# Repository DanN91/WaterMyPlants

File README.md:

# WaterMyPlants

#### Software and Hardware ( ATMega328P ) system aimed to keep our plants alive for a reasonable amount of time while we enjoy our vacation.

Functionalities ( Strategies, changeable at run-time ):
1. **Manual** mode: turn the water pump on/off via a button push;
2. **Timer** mode: turn the water pump on/off for a specific duration of time and with a specific frequency ( once every x days );
3. **Sensor** mode: monitor the soil moisture and calibrate wetness and dryness levels, then water the plants whenever set dryness level is reached, up to the set wetness level.

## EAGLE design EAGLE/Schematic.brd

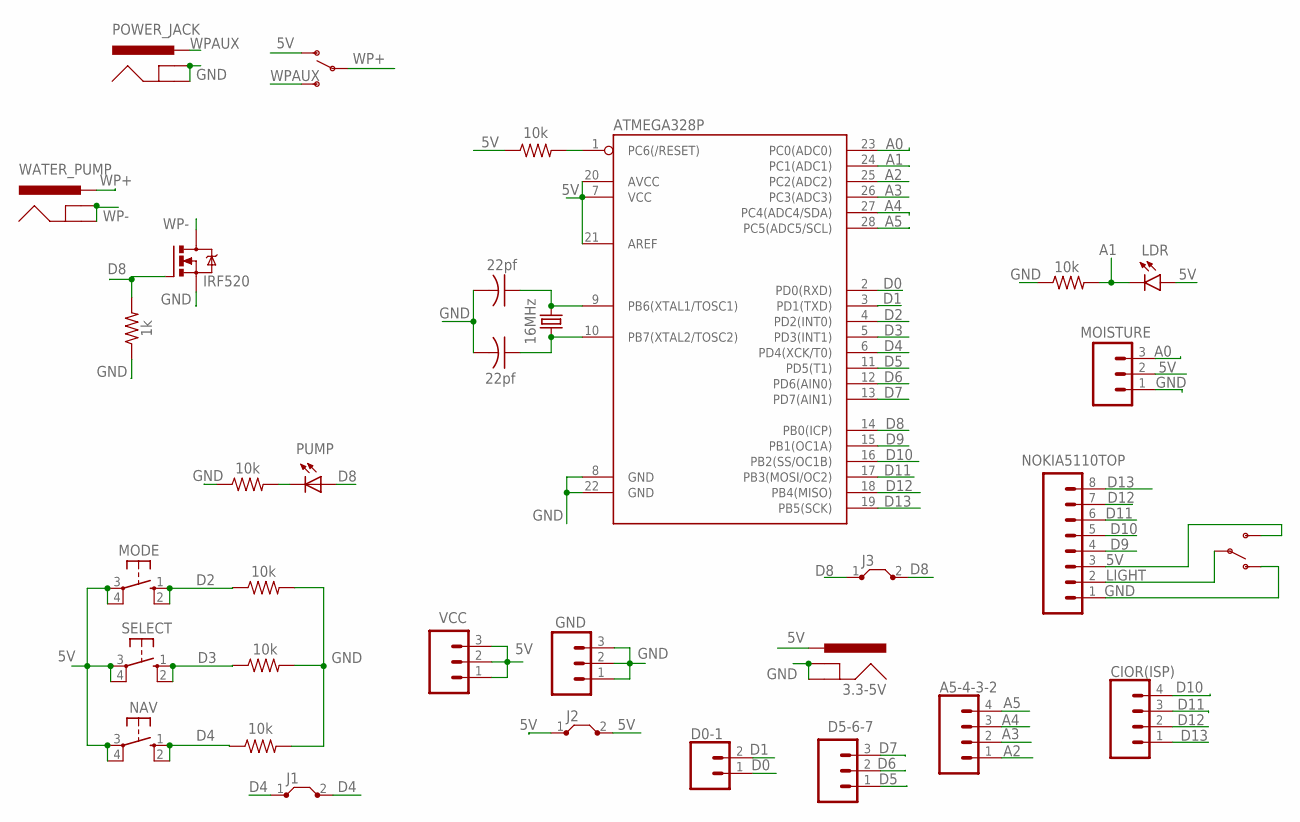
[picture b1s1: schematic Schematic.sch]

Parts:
3.3-5V: POWER_JACK; POWER_JACK_PTH
5V/AUX: SWITCH-SPDT-PTH-11.6X4.0MM-LOCK; SWITCH_SPDT_PTH_11.6X4.0MM_LOCK
A5-4-3-2: CONN_04; 1X04
ATMEGA328P: 328P; DIP28
AUX_POWER: POWER_JACK; POWER_JACK_PTH
C1, C2: 22pf; C025-024X044
CIOR(ISP): CONN_04; 1X04
D0-1: CONN_02; 1X02
D5-6-7: CONN_03; 1X03
GND: CONN_03; 1X03
GND/VCC: SWITCH-SPDT-PTH-11.6X4.0MM-LOCK; SWITCH_SPDT_PTH_11.6X4.0MM_LOCK
J1, J2, J3: J5MM; 05
LDR: LED3MM; LED_3MM
MODE: 10-XX; B3F-10XX
MOISTURE: CONN_03; 1X03
NAV: 10-XX; B3F-10XX
NOKIA5110TOP: CONN_08"; 1X08
PUMP: LED5MM
Q1: IRF520; TO220BV
R2, R3, R4, R5, R7: 10k; AXIAL-0.1
R6: 10k; 0207/2V
R8: 1k; AXIAL-0.1
SELECT: 10-XX; B3F-10XX
VCC: CONN_03; 1X03
WATER_PUMP: WATER_PUMP; POWER_JACK_PTH
Y1: 16MHz; HC49US

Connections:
5V: 3.3-5V.PWR, 5V/AUX.1 (O), ATMEGA328P.7 (VCC), ATMEGA328P.20 (AVCC), ATMEGA328P.21 (AREF), GND/VCC.3 (S), J2.1, J2.2, LDR.A, MODE.3, MODE.4 (P1), MOISTURE.2, NAV.3, NAV.4 (P1), NOKIA5110TOP.3, R7.P$1 (1), SELECT.3, SELECT.4 (P1), VCC.1, VCC.2, VCC.3
A0: ATMEGA328P.23 (PC0(ADC0)), MOISTURE.3
A1: ATMEGA328P.24 (PC1(ADC1)), LDR.K (C), R6.2
A2: A5-4-3-2.1, ATMEGA328P.25 (PC2(ADC2))
A3: A5-4-3-2.2, ATMEGA328P.26 (PC3(ADC3))
A4: A5-4-3-2.3, ATMEGA328P.27 (PC4(ADC4/SDA))
A5: A5-4-3-2.4, ATMEGA328P.28 (PC5(ADC5/SCL))
D0: ATMEGA328P.2 (PD0(RXD)), D0-1.1
D1: ATMEGA328P.3 (PD1(TXD)), D0-1.2
D2: ATMEGA328P.4 (PD2(INT0)), MODE.1 (S), MODE.2 (S1), R5.P$1 (1)
D3: ATMEGA328P.5 (PD3(INT1)), R4.P$1 (1), SELECT.1 (S), SELECT.2 (S1)
D4: ATMEGA328P.6 (PD4(XCK/T0)), J1.1, J1.2, NAV.1 (S), NAV.2 (S1), R3.P$1 (1)
D5: ATMEGA328P.11 (PD5(T1)), D5-6-7.1
D6: ATMEGA328P.12 (PD6(AIN0)), D5-6-7.2
D7: ATMEGA328P.13 (PD7(AIN1)), D5-6-7.3
D8: ATMEGA328P.14 (PB0(ICP)), J3.1, J3.2, PUMP.A, Q1.G, R8.P$2 (2)
D9: ATMEGA328P.15 (PB1(OC1A)), NOKIA5110TOP.4
D10: ATMEGA328P.16 (PB2(SS/OC1B)), CIOR(ISP).4, NOKIA5110TOP.5
D11: ATMEGA328P.17 (PB3(MOSI/OC2)), CIOR(ISP).3, NOKIA5110TOP.6
D12: ATMEGA328P.18 (PB4(MISO)), CIOR(ISP).2, NOKIA5110TOP.7
D13: ATMEGA328P.19 (PB5(SCK)), CIOR(ISP).1, NOKIA5110TOP.8
GND: 3.3-5V.GND, 3.3-5V.GNDBREAK, ATMEGA328P.8 (GND), ATMEGA328P.22 (GND), AUX_POWER.GND, AUX_POWER.GNDBREAK, C1.2, C2.2, GND.1, GND.2, GND.3, GND/VCC.1 (O), MOISTURE.1, NOKIA5110TOP.1, Q1.S, R2.P$1 (1), R3.P$2 (2), R4.P$2 (2), R5.P$2 (2), R6.1, R8.P$1 (1)
LIGHT: GND/VCC.2, NOKIA5110TOP.2
unnamed: PUMP.K (C), R2.P$2 (2)
unnamed: ATMEGA328P.9 (PB6(XTAL1/TOSC1)), C1.1, Y1.2
unnamed: ATMEGA328P.10 (PB7(XTAL2/TOSC2)), C2.1, Y1.1
unnamed: ATMEGA328P.1 (PC6(/RESET)), R7.P$2 (2)
WP+: 5V/AUX.2, WATER_PUMP.PWR
WP-: Q1.D, WATER_PUMP.GND, WATER_PUMP.GNDBREAK
WPAUX: 5V/AUX.3 (S), AUX_POWER.PWR

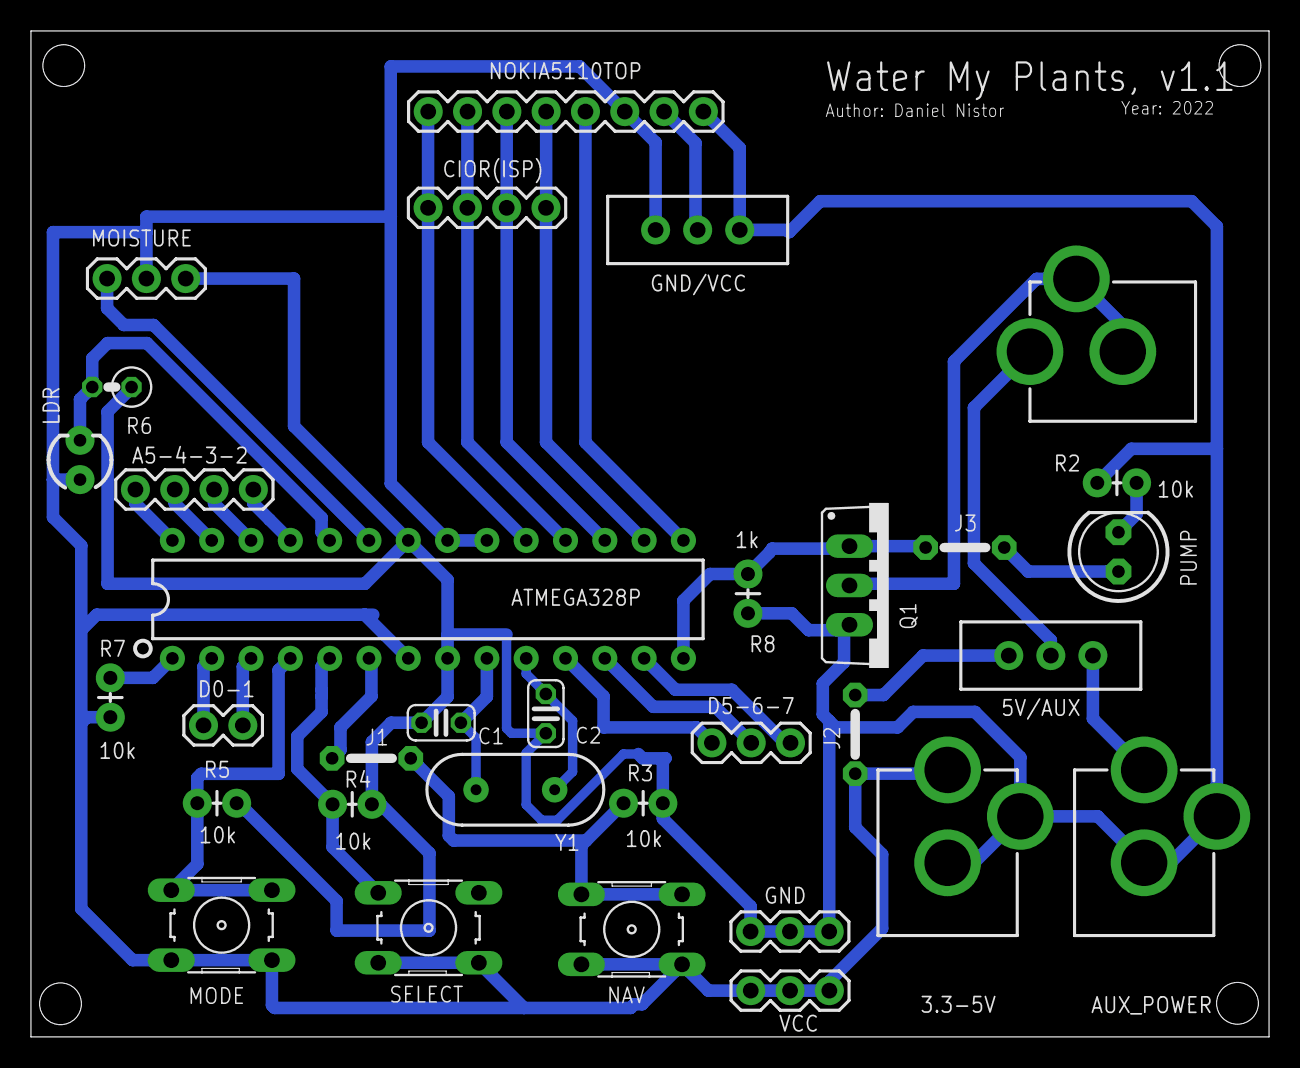
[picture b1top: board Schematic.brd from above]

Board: 2 copper layers, 80.0 x 65.0 mm, 33 parts (0 on the bottom side), 30 nets.

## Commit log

2019-06-27 WaterMyPlants : Implemented manual mode
    Allows you to water your plants with a button push.
2019-06-29 Watering Modes : Manual and Automatic, ugly...
    This is NOT OOP, so I need to refactor it maybe using Strategy Pattern.
    It starts in Auto mode.
    Functionality in Auto mode:
    > Pump ON -> press button -> Manual w Pump OFF.
    > Pump OFF -> press button -> Manual w Pump ON.
    Functionality in Manual mode:
2019-06-29 ATTiny85 : Comment incompatible code
    Use this when compiling for ATTiny85.
2019-06-29 Configured : Water plants once every two days, for one minute
    This is the appropriate time for our flowers.
2019-11-14 WaterMyPlants : Changes description
2019-11-14 WaterMyPlants : Added tomorrow
2019-11-14 Serial : initialize at 9600
2019-11-14 Fix : increase baud rate
2019-11-14 Serial : initialize at 115200
2021-04-02 Added PlatformIO project
2021-04-03 WaterPump : Wrapper over water pump hardware
2021-04-06 Some Cleanup
2021-04-12 Renamed Automatic to TimerMode
2021-04-12 WaterPump: make it non-copyable and non-movable
2021-04-12 Stopwatch: pushbutton controlled
2021-04-12 PushButton: Held, Pressed, Released events
2021-04-13 Modes: added various operation modes
2021-04-13 Iterate through modes and unify constants
2021-04-15 cleanup and reordering
2021-04-15 further cleanup
2021-04-17 OperationModeHandler: use RangeValuesGenerator
2021-04-18 Continue with Menu
2021-04-26 Continue with MenuController
2021-05-15 ChangeSetting: almost implemented it, ToDo: decouple displaying
2021-05-17 Use UniquePtr and updated Observer usage
2021-05-18 OperationModeHandler: Decouple modes creation
2021-05-18 ChangeSetting: added user interaction
2021-05-18 a few fixes
2021-05-18 TimerMode: some fixes
2021-05-20 SensorMode: water plants by night autonomously using a light and a soil moisture sensor
2021-05-21 ToDo:Add support for other types of menu items
2021-06-18 Merge commit from 'cleanup'
    Squashed commits:
    Added PlatformIO project
    WaterPump : Wrapper over water pump hardware
    Some Cleanup
    Renamed Automatic to TimerMode
    WaterPump: make it non-copyable and non-movable
2021-06-18 WaterMyPlants : Implemented 3 operation modes
    Changelog
    Added PlatformIO project
    WaterPump : Wrapper over water pump hardware
    Some Cleanup
    Renamed Automatic to TimerMode
    WaterPump: make it non-copyable and non-movable
2022-03-31 PlatformIO: use C++17 via c++1z flag
2022-06-06 TimerMode: fix time bug and make conditions easier to understand
2022-06-09 EAGLE: Added schematics and board design, todo export gerber
2022-06-11 EAGLE: added gerber files
2022-07-09 Fuses: added .bat for setting the fuses to fit the project's needs
2022-07-09 PlatformIO: add configuration for Uploading by Arduino as ISP
2022-07-09 Hardware: reconfigure based on EAGLE pinout
2022-07-22 TimerMode: use TimerManager for tracking the time
2022-08-03 SensorMode: adapt to real world scenarios
2022-08-04 TimerMode: use TimerEvent for starting and stopping the watering
2022-08-08 continue implementing StandByManager

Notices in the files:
parts and their libraries:
SparkFun-Connectors: Licensing: Creative Commons ShareAlike 4.0 International - https://creativecommons.org/licenses/by-sa/4.0
